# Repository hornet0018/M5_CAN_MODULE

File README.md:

# M5_CAN_MODULE

### Power Node(送信)

#### ID:0x01

- 0 BATT(mv)
- 1 BATT(mv)
- 2 BATT(mv)
- 3 BATT(mv)
- 4 null
- 5 null
- 6 null
- 7 null

### Motor Node(受信)

#### ID:0x02

- 0 speedLeft
- 1 speedLeft
- 2 speedRight
- 3 speedRight
- 4 null
- 5 null
- 6 null
- 7 null

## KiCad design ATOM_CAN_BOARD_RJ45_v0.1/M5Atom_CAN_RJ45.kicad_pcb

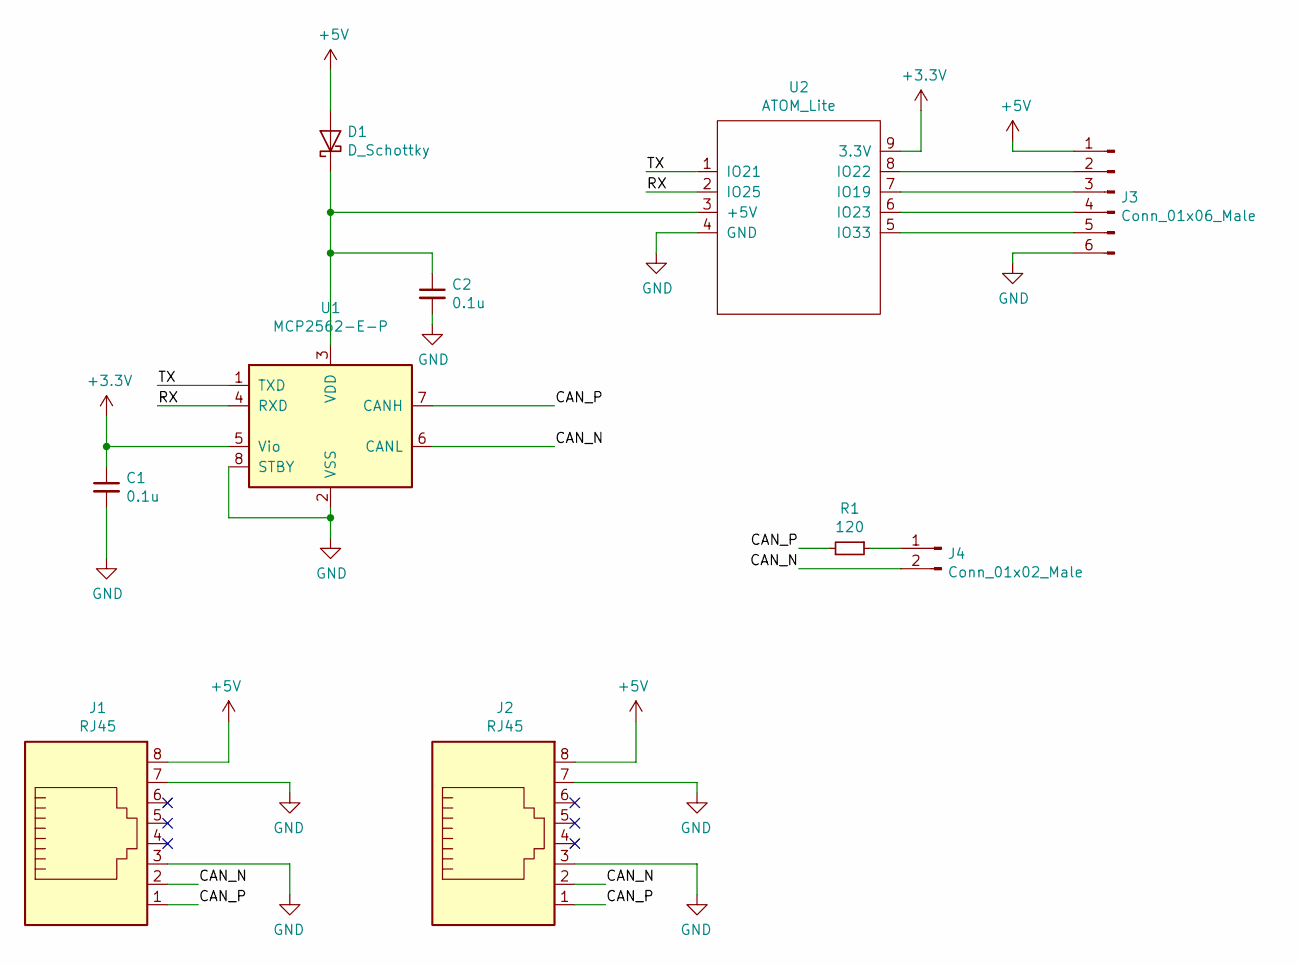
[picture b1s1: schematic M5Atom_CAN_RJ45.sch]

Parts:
C1, C2: 0.1u; C_0603_1608Metric_Pad1.05x0.95mm_HandSolder
D1: D_Schottky; D_TUMD2
J1, J2: RJ45; 7810-8P8C
J3: Conn_01x06_Male; B06BPASKLFSN
J4: Conn_01x02_Male; PinHeader_1x02_P2.54mm_Vertical
R1: 120; R_0603_1608Metric_Pad1.05x0.95mm_HandSolder
U1: MCP2562-E-P; SOIC-8_3.9x4.9mm_P1.27mm
U2: ATOM_Lite; M5ATOM

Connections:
+3V3: C1.1, U1.5 (Vio), U2.9 (3.3V)
+5V: D1.2 (A), J1.8, J2.8, J3.1
/CAN_N: J1.2, J2.2, J4.2, U1.6 (CANL)
/CAN_P: J1.1, J2.1, R1.2, U1.7 (CANH)
/RX: U1.4 (RXD), U2.2 (IO25)
/TX: U1.1 (TXD), U2.1 (IO21)
GND: C1.2, C2.2, J1.3, J1.7, J2.3, J2.7, J3.6, U1.2 (VSS), U1.8 (STBY), U2.4 (GND)
unnamed: C2.1, D1.1 (K), U1.3 (VDD), U2.3 (+5V)
unnamed: J3.2, U2.8 (IO22)
unnamed: J3.3, U2.7 (IO19)
unnamed: J3.4, U2.6 (IO23)
unnamed: J3.5, U2.5 (IO33)
unnamed: J4.1, R1.1

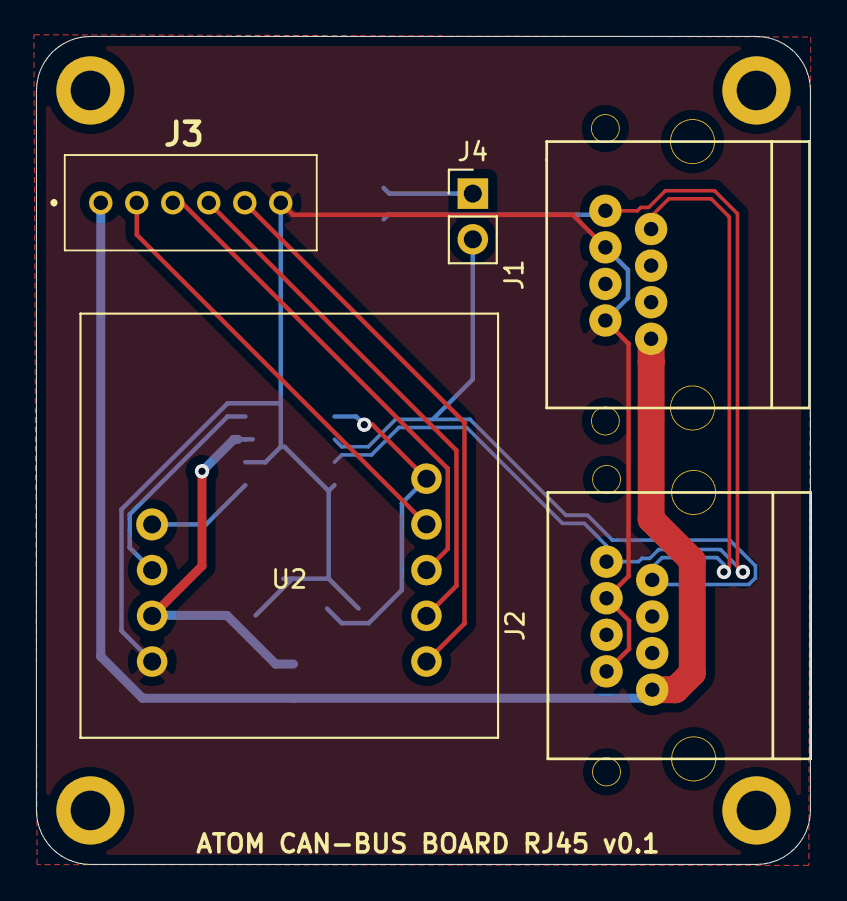
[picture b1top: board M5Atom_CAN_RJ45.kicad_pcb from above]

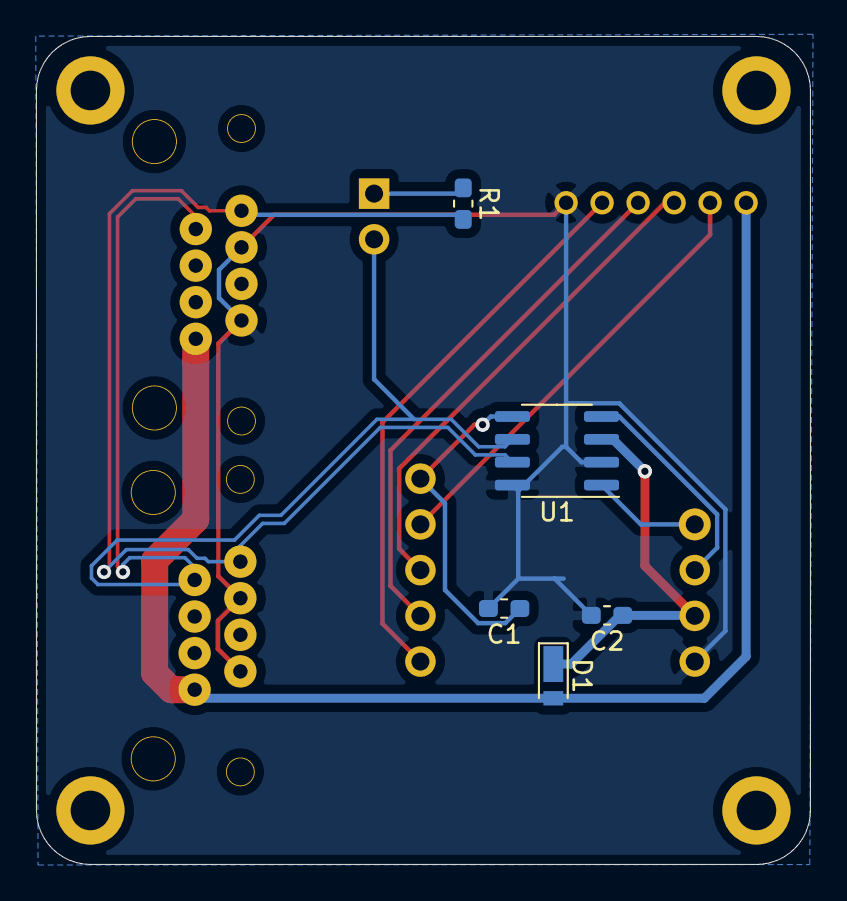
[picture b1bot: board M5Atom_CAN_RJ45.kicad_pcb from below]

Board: 2 copper layers, 43.0 x 46.0 mm, 10 parts (5 on the bottom side), 13 nets.

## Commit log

2020-12-05 update_PCB
2021-01-12 ATOM_CAN_BOARD_v0.2 and RJ45_v0.1 update
